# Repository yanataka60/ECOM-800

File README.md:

# ECOM-800

　トランジスタ技術 1977年10月号から1978年1月号にかけて連載されていた「マイコンピュータをつくろう(SC/MP編)」のECOM-800の基板を起こしました。

## 回路図
　KiCadフォルダ内のECOM-800.pdfを参照してください。

　掲載されている回路から以下の変更をしています。

　・ワンボードとするためにロータリースイッチをスライドスイッチに変更しています。

　・81LS95を74LS244に変更しています。

　・SRAMを6264としています。

　・SRAMのバッテリーバックアップを付加しました。

[回路図](https://github.com/yanataka60/ECOM-800/blob/main/Kicad/ECOM-800.pdf)

## 部品表
|番号|品名|数量|備考|
| ------------ | ------------ | ------------ | ------------ |
|C1-C12|積層セラミックコンデンサ 0.1uF|12||
|C13|電解コンデンサ 100uF|1||
|C14,C15|積層セラミックコンデンサ 270pF|2||
|D1-D11|5mm赤色LED|11|秋月電子通商 OSDR5113Aなど|
|D12-D13|ダイオード 1S4|2|秋月電子通商など|
|J1|DCジャック|1|秋月電子通商 MJ-179PHなど|
|J2|3Pスライドスイッチ又は1x3ピンヘッダとジャンパーピン|1|秋月電子通商 SS12D01G4又はPH-1X3SG,MJ-254-6BK等|
|R2,R3,R5,R11,R12|カーボン抵抗 10k|5||
|R13,R14|カーボン抵抗 3.3k|2||
|R15|カーボン抵抗 500Ω|1||
|R16,R17|カーボン抵抗 1k|2||
|RN1|集合抵抗 1k×8|1|秋月電子通商 RKC8BD102Jなど|
|RN2-RN4|集合抵抗 10k×8|3|秋月電子通商 RKC8BD103Jなど|
|S1|3Pスライドスイッチ|1|秋月電子通商 SS12D01G4など|
|SW1,SW6|3Pプッシュスイッチ|2|共立エレショップ MS-650B-C-P-N/Rなど|
|SW3-SW5|1回路3接点 小型スライドスイッチ|3|Amazon,楽天市場,aitendo SS13D07など|
|SW2,SW7-SW22|3Pトグルスイッチ|17|共立エレショップ 2MS1-T1-B1-M2-QNなど|
|U1,U5|74LS04|2|樫木総業等|
|U2|74LS00|1|樫木総業等|
|U3|74LS279|1|樫木総業等|
|U4|SC/MPⅡ(INS8060)|1|ebay等(不良品多し)|
|U6|74LS02|1|樫木総業等|
|U7|SRAM 6264|1|若松通商等|
|U8|74LS51|1|樫木総業等|
|U9,U10|74LS375|2|樫木総業等|
|U11,U12|74LS244|2|樫木総業等|
|BT1|ボタン電池基板取付用ホルダー CR2032用(縦型)|1|秋月電子通商 CH243-2032LFなど|

## 組み立ての注意点
　SW1の取付向きに注意してください。押されていない状態で上側がONとなるようにつけます。

## ボードの完成写真

## バッテリーバックアップ
　J2のEXT側でCR2032でのバックアップになり、IN側で電源ラインでのバックアップになります。

　CR2032を使わなくても電源に電池等を使ってIN側しておけば電池を外さない限りバックアップされます。

　なお、ECOM-800の回路の特性として電源スイッチがONになった時にデータ・スイッチ(D0～D7)の状態がメモリ0000hに書き込まれてしまうようです。(アドレススイッチの状態に関係なく、0000hに書き込まれます)

　0000hに意図して書き込んだ内容が勝手に書き換わってしまいますが、SC/MPⅡで0000hは実行されませんので書き換わってしまっても影響はありません。

## ECOM-800掲載個所
　トランジスタ技術

　　 1977年10月号 P238～P247

　　 1977年11月号 P266～P275

　　 1977年12月号 P262～P271

　　 1978年 1月号 P267～P277

## SAMPLEプログラム
　記事に掲載されている回転プログラムを発展させ、ナイトライダー風にしてみました。

　sampleフォルダ中のsample.lst又はsample.binを参照して入力してください。

## 利用上の注意
　KiCADデータおよびガーバーデータはCC BY-SA 4.0 (Copyright (C) 2024 Kazuhiro Ouchi)です。  

## 謝辞
　トグルスイッチ、プッシュスイッチのKiCADデータは、かんぱぱ様の「COSMAC Toy Computer Version 2」を使わせていただきました。

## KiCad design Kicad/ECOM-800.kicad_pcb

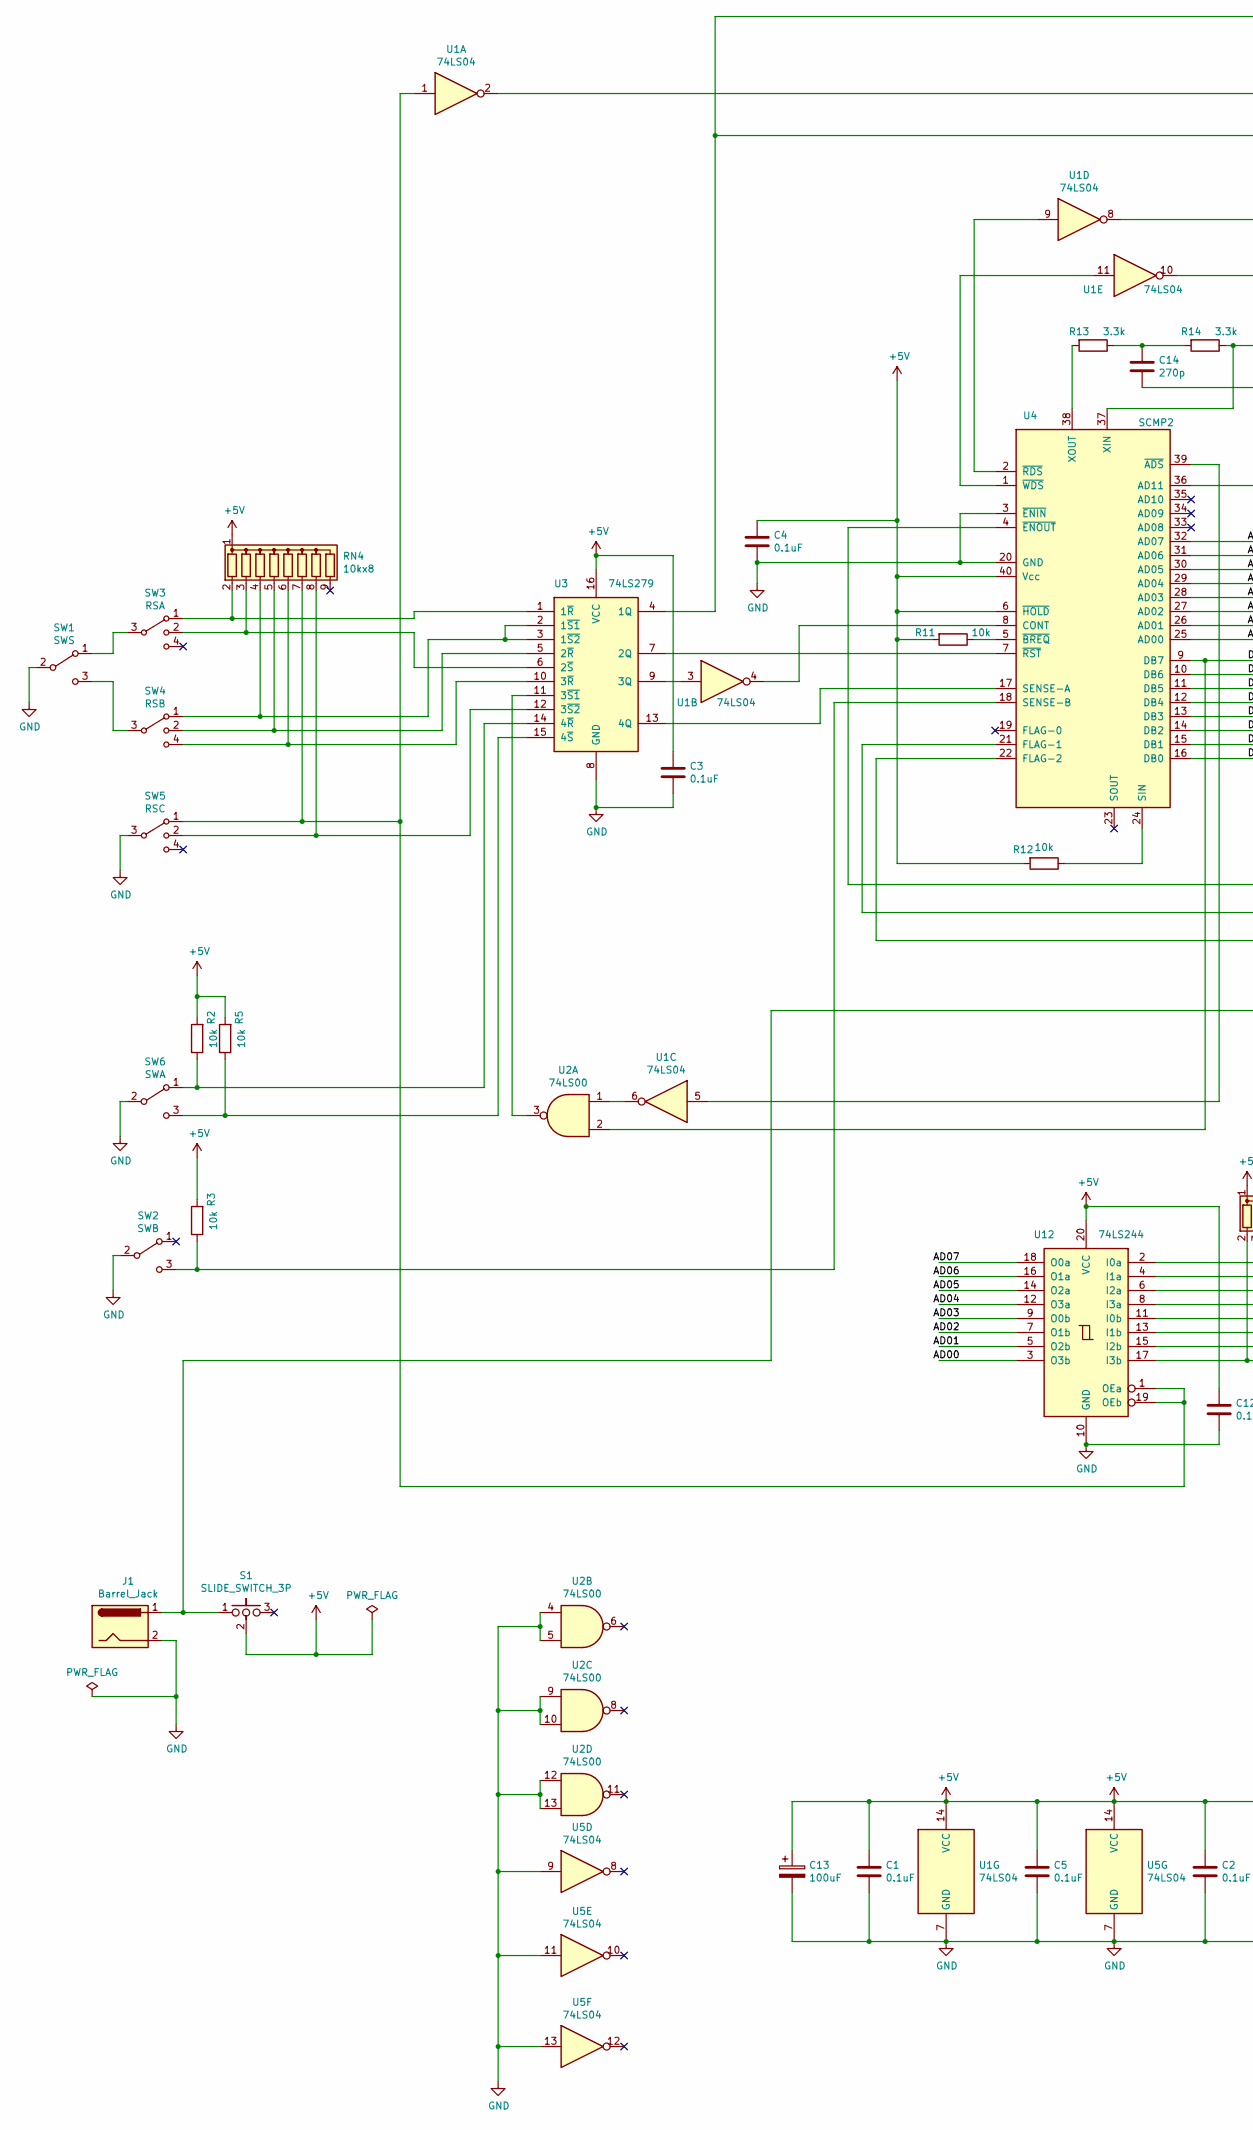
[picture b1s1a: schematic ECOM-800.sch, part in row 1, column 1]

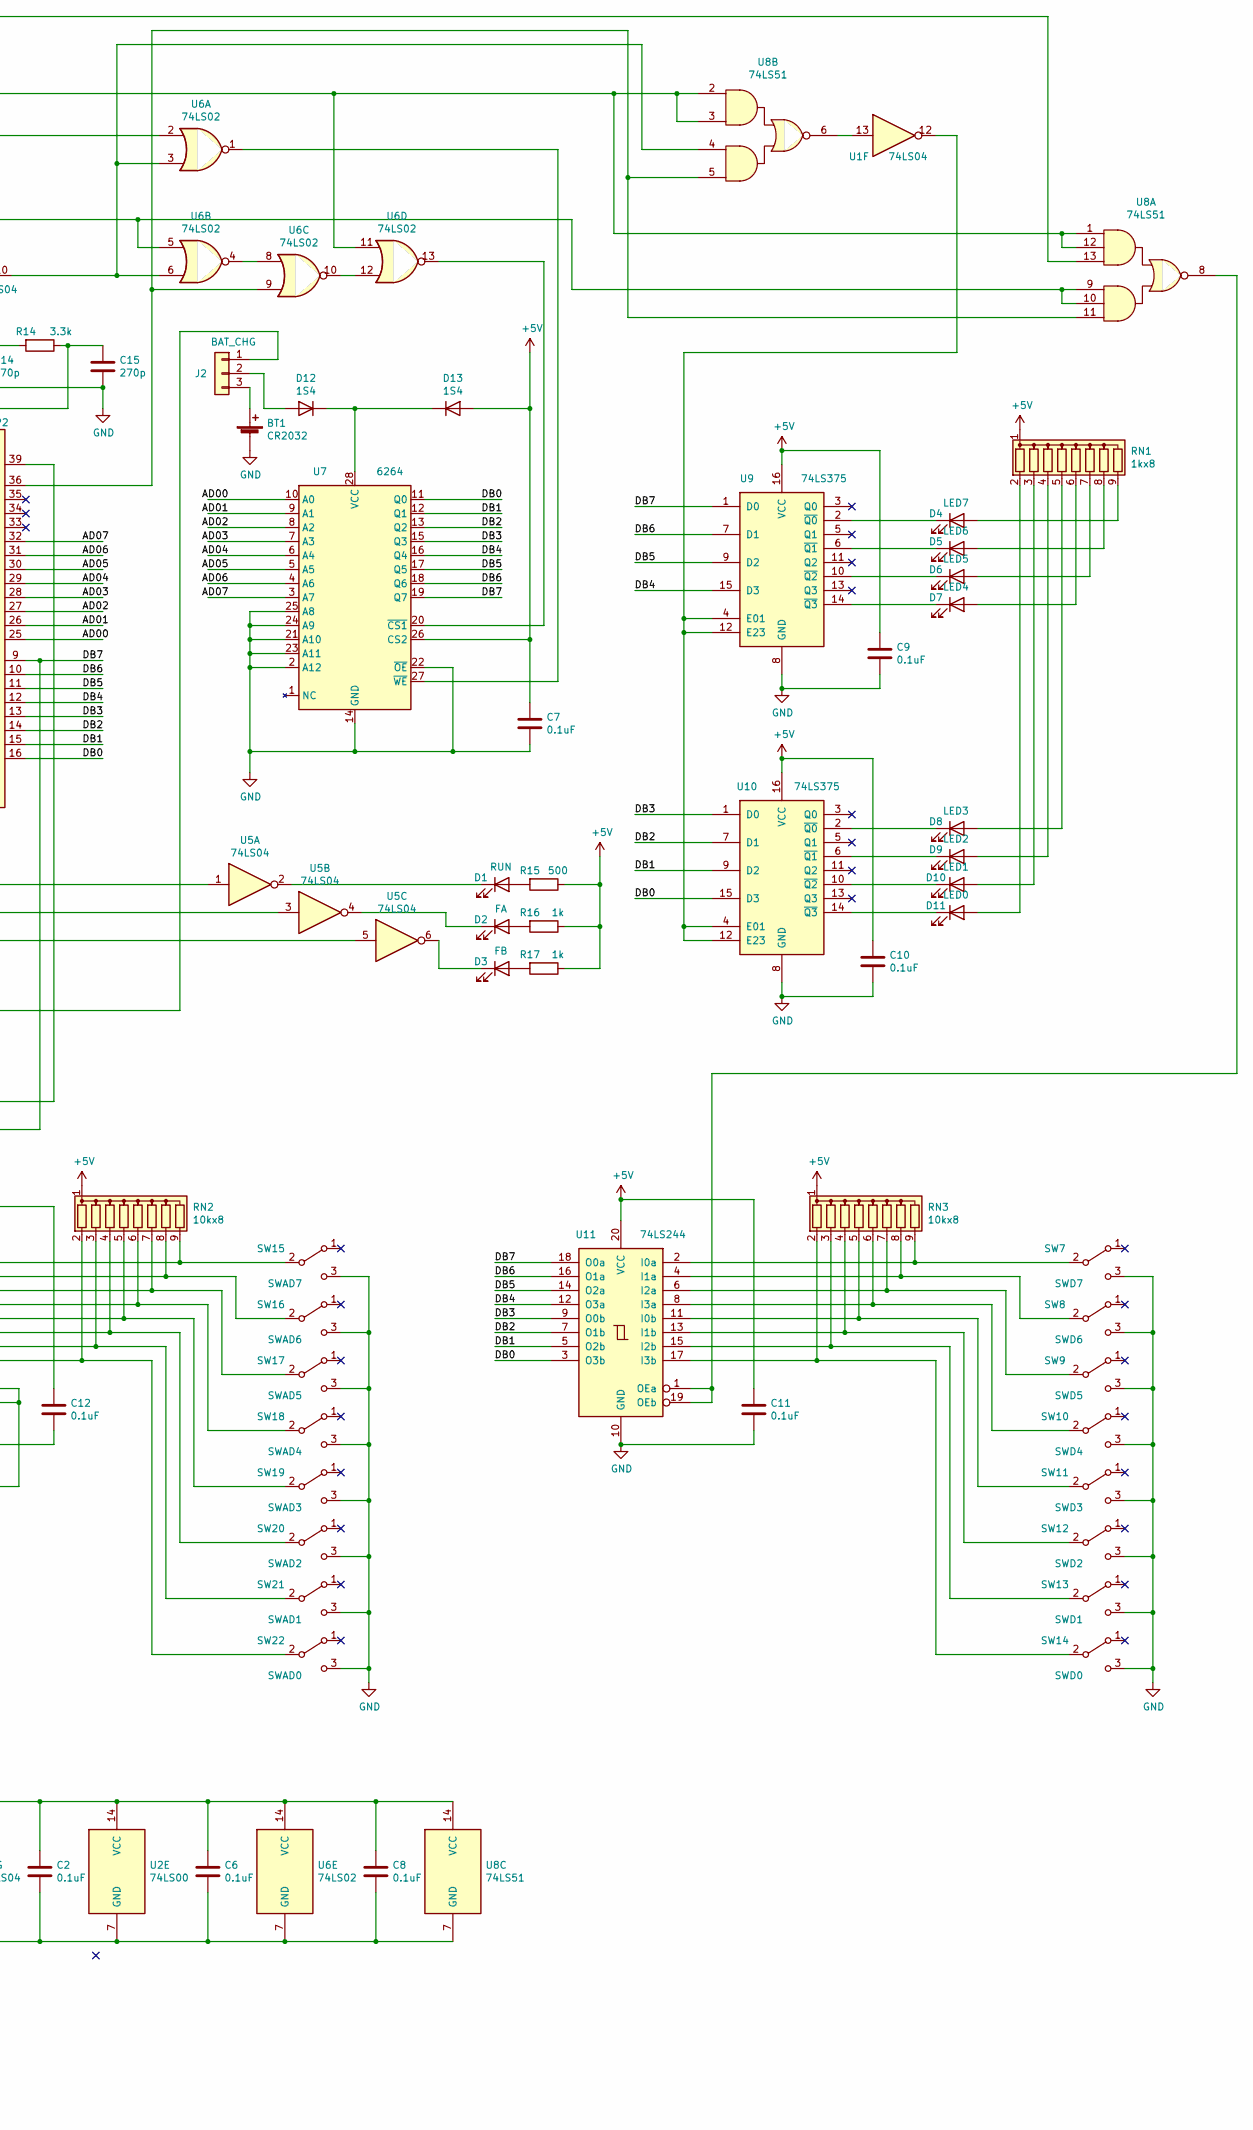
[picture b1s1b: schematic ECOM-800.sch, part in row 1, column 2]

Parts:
BT1: CR2032; Battery_CR2032
C1, C2, C3, C4, C5, C6, C7, C8, C9, C10, C11, C12: 0.1uF; C_Rect_L4.0mm_W2.5mm_P2.50mm
C13: 100uF; CP_Radial_D5.0mm_P2.50mm
C14, C15: 270p; C_Rect_L4.0mm_W2.5mm_P2.50mm
D1: RUN; LED_D5.0mm
D2: FA; LED_D5.0mm
D3: FB; LED_D5.0mm
D4: LED7; LED_D5.0mm
D5: LED6; LED_D5.0mm
D6: LED5; LED_D5.0mm
D7: LED4; LED_D5.0mm
D8: LED3; LED_D5.0mm
D9: LED2; LED_D5.0mm
D10: LED1; LED_D5.0mm
D11: LED0; LED_D5.0mm
D12, D13: 1S4; D_DO-41_SOD81_P10.16mm_Horizontal
J1: Barrel_Jack; BarrelJack_Horizontal
J2: BAT_CHG; PinHeader_1x03_P2.54mm_Vertical
R2, R3, R5, R11, R12: 10k; R_Axial_DIN0207_L6.3mm_D2.5mm_P10.16mm_Horizontal
R13, R14: 3.3k; R_Axial_DIN0207_L6.3mm_D2.5mm_P10.16mm_Horizontal
R15: 500; R_Axial_DIN0207_L6.3mm_D2.5mm_P10.16mm_Horizontal
R16, R17: 1k; R_Axial_DIN0207_L6.3mm_D2.5mm_P10.16mm_Horizontal
RN1: 1kx8; R_Array_SIP9
RN2, RN3, RN4: 10kx8; R_Array_SIP9
S1: SLIDE_SWITCH_3P; PinHeader_1x03_P2.54mm_Vertical
SW1: SWS; SW_Toggle_P2.54mm_Vertical
SW2: SWB; SW_Toggle_P2.54mm_Vertical
SW3: RSA; Slide_Switch_1x3
SW4: RSB; Slide_Switch_1x3
SW5: RSC; Slide_Switch_1x3
SW6: SWA; SW_Toggle_P2.54mm_Vertical
SW7: SWD7; SW_Toggle_P2.54mm_Vertical
SW8: SWD6; SW_Toggle_P2.54mm_Vertical
SW9: SWD5; SW_Toggle_P2.54mm_Vertical
SW10: SWD4; SW_Toggle_P2.54mm_Vertical
SW11: SWD3; SW_Toggle_P2.54mm_Vertical
SW12: SWD2; SW_Toggle_P2.54mm_Vertical
SW13: SWD1; SW_Toggle_P2.54mm_Vertical
SW14: SWD0; SW_Toggle_P2.54mm_Vertical
SW15: SWAD7; SW_Toggle_P2.54mm_Vertical
SW16: SWAD6; SW_Toggle_P2.54mm_Vertical
SW17: SWAD5; SW_Toggle_P2.54mm_Vertical
SW18: SWAD4; SW_Toggle_P2.54mm_Vertical
SW19: SWAD3; SW_Toggle_P2.54mm_Vertical
SW20: SWAD2; SW_Toggle_P2.54mm_Vertical
SW21: SWAD1; SW_Toggle_P2.54mm_Vertical
SW22: SWAD0; SW_Toggle_P2.54mm_Vertical
U1, U5: 74LS04; DIP-14_W7.62mm_LongPads
U2: 74LS00; DIP-14_W7.62mm_LongPads
U3: 74LS279; DIP-16_W7.62mm_LongPads
U4: SCMP2; DIP-40_W15.24mm_LongPads
U6: 74LS02; DIP-14_W7.62mm_LongPads
U7: 6264; DIP-28_W15.24mm_LongPads
U8: 74LS51; DIP-14_W7.62mm_LongPads
U9, U10: 74LS375; DIP-16_W7.62mm_LongPads
U11, U12: 74LS244; DIP-20_W7.62mm_LongPads

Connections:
+5V: C1.1, C2.1, C3.1, C4.1, C5.1, C6.1, C7.1, C8.1, C9.1, C10.1, C11.1, C12.1, C13.1, D13.2 (A), R2.2, R3.2, R5.2, R11.2, R12.2, R15.1, R16.1, R17.1, RN1.1 (common), RN2.1 (common), RN3.1 (common), RN4.1 (common), S1.2, U1.14 (VCC), U2.14 (VCC), U3.16 (VCC), U4.6 (~HOLD), U4.40 (Vcc), U5.14 (VCC), U6.14 (VCC), U7.26 (CS2), U8.14 (VCC), U9.16 (VCC), U10.16 (VCC), U11.20 (VCC), U12.20 (VCC)
/AD00: U4.25 (AD00), U7.10 (A0), U12.3 (O3b)
/AD01: U4.26 (AD01), U7.9 (A1), U12.5 (O2b)
/AD02: U4.27 (AD02), U7.8 (A2), U12.7 (O1b)
/AD03: U4.28 (AD03), U7.7 (A3), U12.9 (O0b)
/AD04: U4.29 (AD04), U7.6 (A4), U12.12 (O3a)
/AD05: U4.30 (AD05), U7.5 (A5), U12.14 (O2a)
/AD06: U4.31 (AD06), U7.4 (A6), U12.16 (O1a)
/AD07: U4.32 (AD07), U7.3 (A7), U12.18 (O0a)
/DB0: U4.16 (DB0), U7.11 (Q0), U10.15 (D3), U11.3 (O3b)
/DB1: U4.15 (DB1), U7.12 (Q1), U10.9 (D2), U11.5 (O2b)
/DB2: U4.14 (DB2), U7.13 (Q2), U10.7 (D1), U11.7 (O1b)
/DB3: U4.13 (DB3), U7.15 (Q3), U10.1 (D0), U11.9 (O0b)
/DB4: U4.12 (DB4), U7.16 (Q4), U9.15 (D3), U11.12 (O3a)
/DB5: U4.11 (DB5), U7.17 (Q5), U9.9 (D2), U11.14 (O2a)
/DB6: U4.10 (DB6), U7.18 (Q6), U9.7 (D1), U11.16 (O1a)
/DB7: U2.2, U4.9 (DB7), U7.19 (Q7), U9.1 (D0), U11.18 (O0a)
GND: BT1.2 (-), C1.2, C2.2, C3.2, C4.2, C5.2, C6.2, C7.2, C8.2, C9.2, C10.2, C11.2, C12.2, C13.2, C14.2, C15.2, J1.2, SW1.2 (B), SW2.2 (B), SW5.3, SW6.2 (B), SW7.3 (C), SW8.3 (C), SW9.3 (C), SW10.3 (C), SW11.3 (C), SW12.3 (C), SW13.3 (C), SW14.3 (C), SW15.3 (C), SW16.3 (C), SW17.3 (C), SW18.3 (C), SW19.3 (C), SW20.3 (C), SW21.3 (C), SW22.3 (C), U1.7 (GND), U2.4, U2.5, U2.7 (GND), U2.9, U2.10, U2.12, U2.13, U3.8 (GND), U4.3 (~ENIN), U4.20 (GND), U5.7 (GND), U5.9, U5.11, U5.13, U6.7 (GND), U7.2 (A12), U7.14 (GND), U7.21 (A10), U7.22 (~OE), U7.23 (A11), U7.24 (A9), U7.25 (A8), U8.7 (GND), U9.8 (GND), U10.8 (GND), U11.10 (GND), U12.10 (GND)
unnamed: BT1.1 (+), J2.3
unnamed: C14.1, R13.1, R14.2
unnamed: C15.1, R14.1, U4.37 (XIN)
unnamed: D1.1 (K), U5.2
unnamed: D1.2 (A), R15.2
unnamed: D2.1 (K), U5.4
unnamed: D2.2 (A), R16.2
unnamed: D3.1 (K), U5.6
unnamed: D3.2 (A), R17.2
unnamed: D4.1 (K), U9.2 (~Q0)
unnamed: D4.2 (A), RN1.9 (R8)
unnamed: D5.1 (K), U9.6 (~Q1)
unnamed: D5.2 (A), RN1.8 (R7)
unnamed: D6.1 (K), U9.10 (~Q2)
unnamed: D6.2 (A), RN1.7 (R6)
unnamed: D7.1 (K), U9.14 (~Q3)
unnamed: D7.2 (A), RN1.6 (R5)
unnamed: D8.1 (K), U10.2 (~Q0)
unnamed: D8.2 (A), RN1.5 (R4)
unnamed: D9.1 (K), U10.6 (~Q1)
unnamed: D9.2 (A), RN1.4 (R3)
unnamed: D10.1 (K), U10.10 (~Q2)
unnamed: D10.2 (A), RN1.3 (R2)
unnamed: D11.1 (K), U10.14 (~Q3)
unnamed: D11.2 (A), RN1.2 (R1)
unnamed: D12.1 (K), D13.1 (K), U7.28 (VCC)
unnamed: D12.2 (A), J2.2
unnamed: J1.1, J2.1, S1.1
unnamed: R2.1, SW6.1 (A), U3.14 (4~R)
unnamed: R3.1, SW2.3 (C), U4.18 (SENSE-B)
unnamed: R5.1, SW6.3 (C), U3.15 (4~S)
unnamed: R11.1, U4.5 (~BREQ)
unnamed: R12.1, U4.24 (SIN)
unnamed: R13.2, U4.38 (XOUT)
unnamed: RN2.2 (R1), SW22.2 (B), U12.17 (I3b)
unnamed: RN2.3 (R2), SW21.2 (B), U12.15 (I2b)
unnamed: RN2.4 (R3), SW20.2 (B), U12.13 (I1b)
unnamed: RN2.5 (R4), SW19.2 (B), U12.11 (I0b)
unnamed: RN2.6 (R5), SW18.2 (B), U12.8 (I3a)
unnamed: RN2.7 (R6), SW17.2 (B), U12.6 (I2a)
unnamed: RN2.8 (R7), SW16.2 (B), U12.4 (I1a)
unnamed: RN2.9 (R8), SW15.2 (B), U12.2 (I0a)
unnamed: RN3.2 (R1), SW14.2 (B), U11.17 (I3b)
unnamed: RN3.3 (R2), SW13.2 (B), U11.15 (I2b)
unnamed: RN3.4 (R3), SW12.2 (B), U11.13 (I1b)
unnamed: RN3.5 (R4), SW11.2 (B), U11.11 (I0b)
unnamed: RN3.6 (R5), SW10.2 (B), U11.8 (I3a)
unnamed: RN3.7 (R6), SW9.2 (B), U11.6 (I2a)
unnamed: RN3.8 (R7), SW8.2 (B), U11.4 (I1a)
unnamed: RN3.9 (R8), SW7.2 (B), U11.2 (I0a)
unnamed: RN4.2 (R1), SW3.1, U3.1 (1~R)
unnamed: RN4.3 (R2), SW3.2, U3.6 (2~S)
unnamed: RN4.4 (R3), SW4.1, U3.2 (1~S1), U3.3 (1~S2)
unnamed: RN4.5 (R4), SW4.2, U3.5 (2~R)
unnamed: RN4.6 (R5), SW4.4, U3.10 (3~R)
unnamed: RN4.7 (R6), SW5.1, U1.1, U12.1 (OEa), U12.19 (OEb)
unnamed: RN4.8 (R7), SW5.2, U3.12 (3~S2)
unnamed: SW1.1 (A), SW3.3
unnamed: SW1.3 (C), SW4.3
unnamed: U1.2, U6.11, U8.1, U8.2, U8.3, U8.12
unnamed: U1.3, U3.9 (3Q)
unnamed: U1.4, U4.8 (CONT)
unnamed: U1.5, U4.39 (~ADS)
unnamed: U1.6, U2.1
unnamed: U1.8, U6.5, U8.9, U8.10
unnamed: U1.9, U4.2 (~RDS)
unnamed: U1.10, U6.3, U6.6, U8.4
unnamed: U1.11, U4.1 (~WDS)
unnamed: U1.12, U9.4 (E01), U9.12 (E23), U10.4 (E01), U10.12 (E23)
unnamed: U1.13, U8.6
unnamed: U2.3, U3.11 (3~S1)
unnamed: U3.4 (1Q), U6.2, U8.13
unnamed: U3.7 (2Q), U4.7 (~RST)
unnamed: U3.13 (4Q), U4.17 (SENSE-A)
unnamed: U4.4 (~ENOUT), U5.1
unnamed: U4.21 (FLAG-1), U5.3
unnamed: U4.22 (FLAG-2), U5.5
unnamed: U4.36 (AD11), U6.9, U8.5, U8.11
unnamed: U6.1, U7.27 (~WE)
unnamed: U6.4, U6.8
unnamed: U6.10, U6.12
unnamed: U6.13, U7.20 (~CS1)
unnamed: U8.8, U11.1 (OEa), U11.19 (OEb)

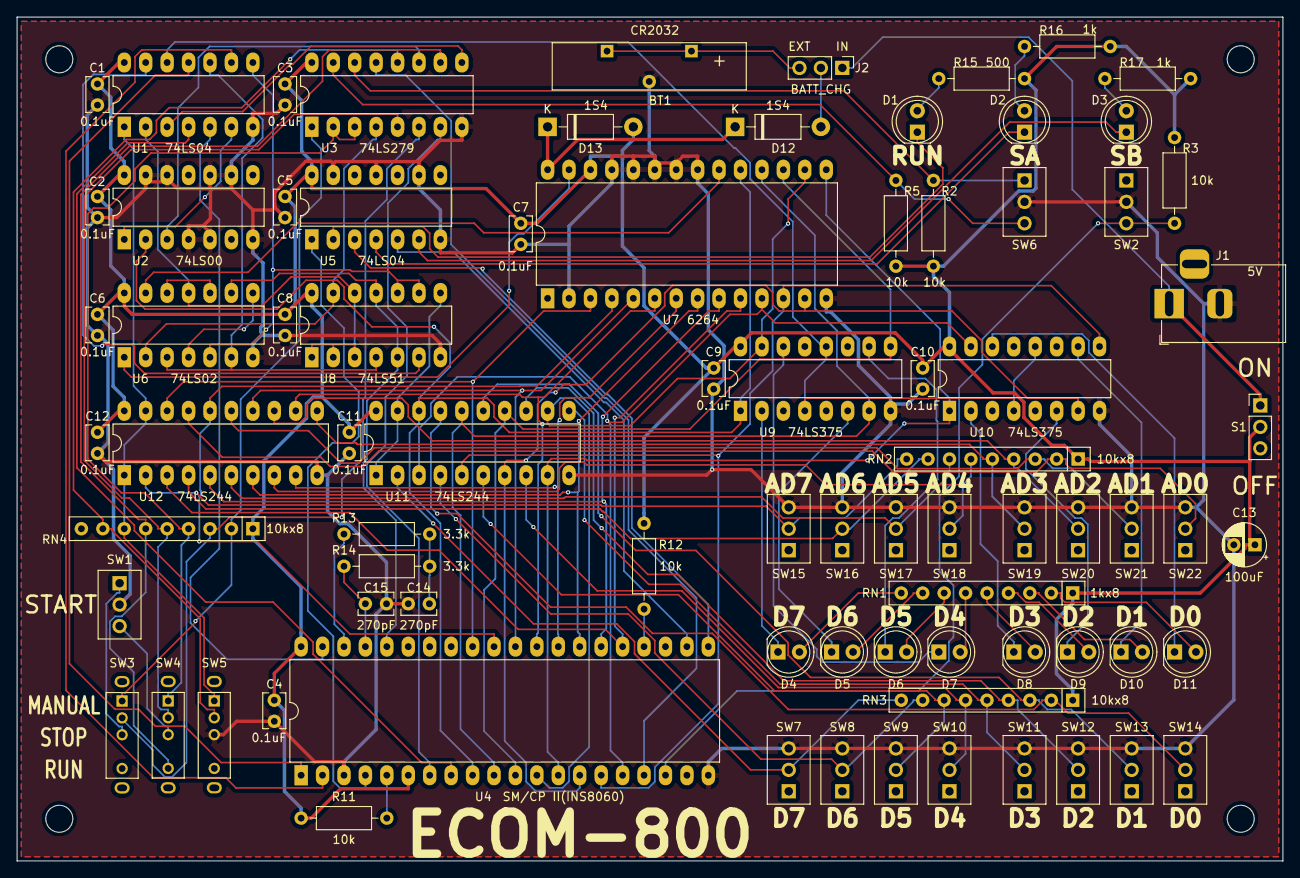
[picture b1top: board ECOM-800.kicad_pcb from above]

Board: 2 copper layers, 150.0 x 100.0 mm, 84 parts (0 on the bottom side), 101 nets.

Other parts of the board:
MH1, MH2, MH3, MH4: MountingHole_3.2mm_M3
